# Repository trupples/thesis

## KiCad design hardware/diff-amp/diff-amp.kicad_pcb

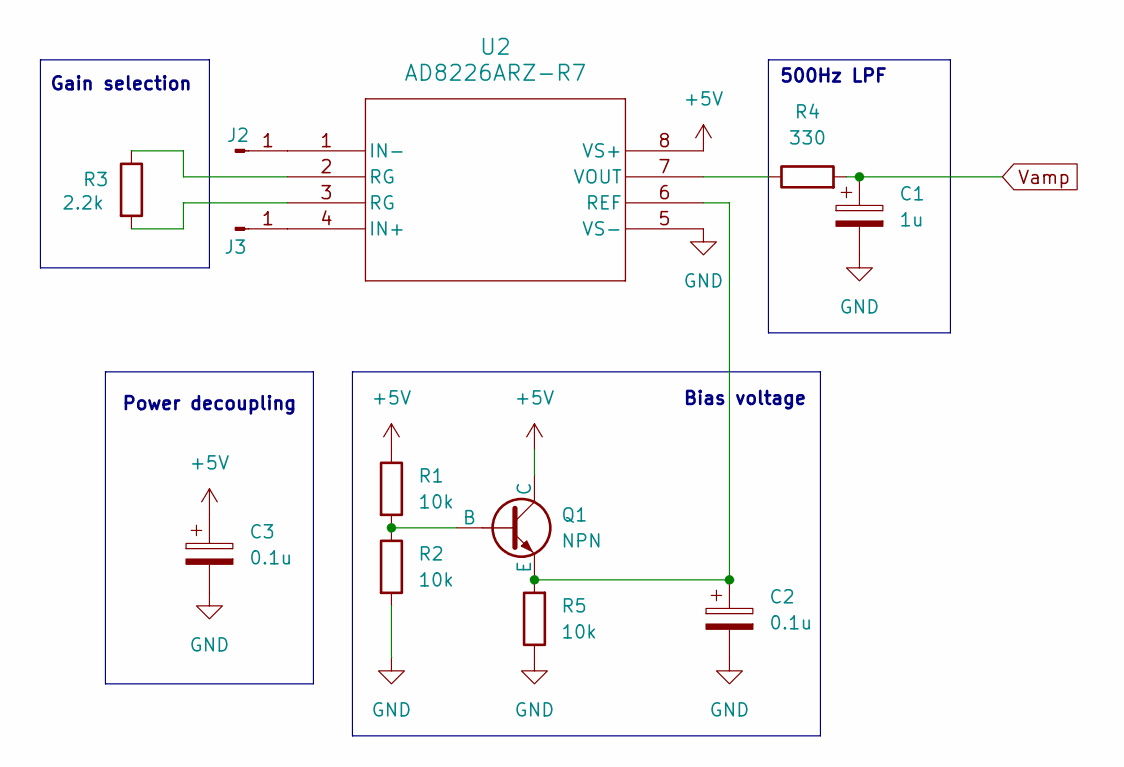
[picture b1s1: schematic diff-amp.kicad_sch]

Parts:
C1: 1u; CP_Radial_D4.0mm_P2.00mm
C2, C3: 0.1u; CP_Radial_D5.0mm_P2.50mm
J2, J3: Conn_01x01_Pin; SolderWirePad_1x01_SMD_5x10mm
Q1: NPN; TO-92L_Inline_Wide
R1, R2, R5: 10k; R_Axial_DIN0207_L6.3mm_D2.5mm_P2.54mm_Vertical
R3: 2.2k; R_Axial_DIN0207_L6.3mm_D2.5mm_P7.62mm_Horizontal
R4: 330; R_Axial_DIN0207_L6.3mm_D2.5mm_P10.16mm_Horizontal
U2: AD8226ARZ-R7; DIP-8_W7.62mm_Socket

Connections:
+5V: C3.1, Q1.1 (C), R1.1, U2.8 (VS+); also elsewhere on the board
GND: C1.2, C2.2, C3.2, R2.2, R5.1, U2.5 (VS-); also elsewhere on the board
unnamed: J2.1, U2.1 (IN-)
unnamed: J3.1, U2.4 (IN+)
unnamed: Q1.2 (B), R1.2, R2.1
unnamed: C2.1, Q1.3 (E), R5.2, U2.6 (REF)
unnamed: R3.1, U2.2 (RG)
unnamed: R3.2, U2.3 (RG)
unnamed: R4.1, U2.7 (VOUT)
Vout: C1.1, R4.2; also elsewhere on the board

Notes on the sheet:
500Hz LPF
Power decoupling
Gain selection
Bias voltage

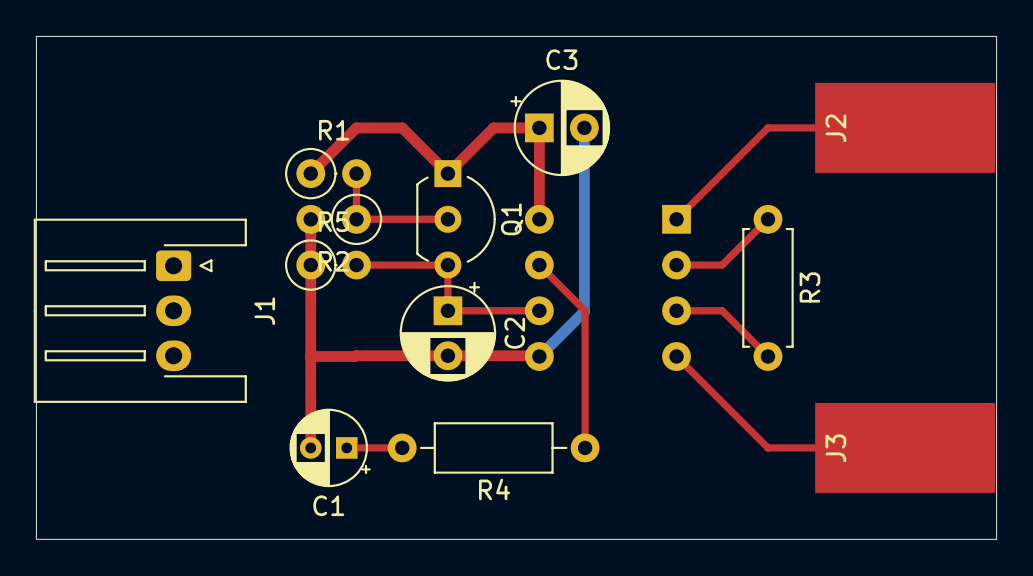
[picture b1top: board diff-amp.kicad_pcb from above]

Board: 2 copper layers, 53.3 x 27.9 mm, 13 parts (1 on the bottom side), 10 nets.

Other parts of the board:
J1: Conn_01x03_Socket; JST_XH_S3B-XH-A-1_1x03_P2.50mm_Horizontal

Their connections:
+5V: J1.1; also elsewhere on the board
GND: J1.2; also elsewhere on the board
Vout: J1.3; also elsewhere on the board

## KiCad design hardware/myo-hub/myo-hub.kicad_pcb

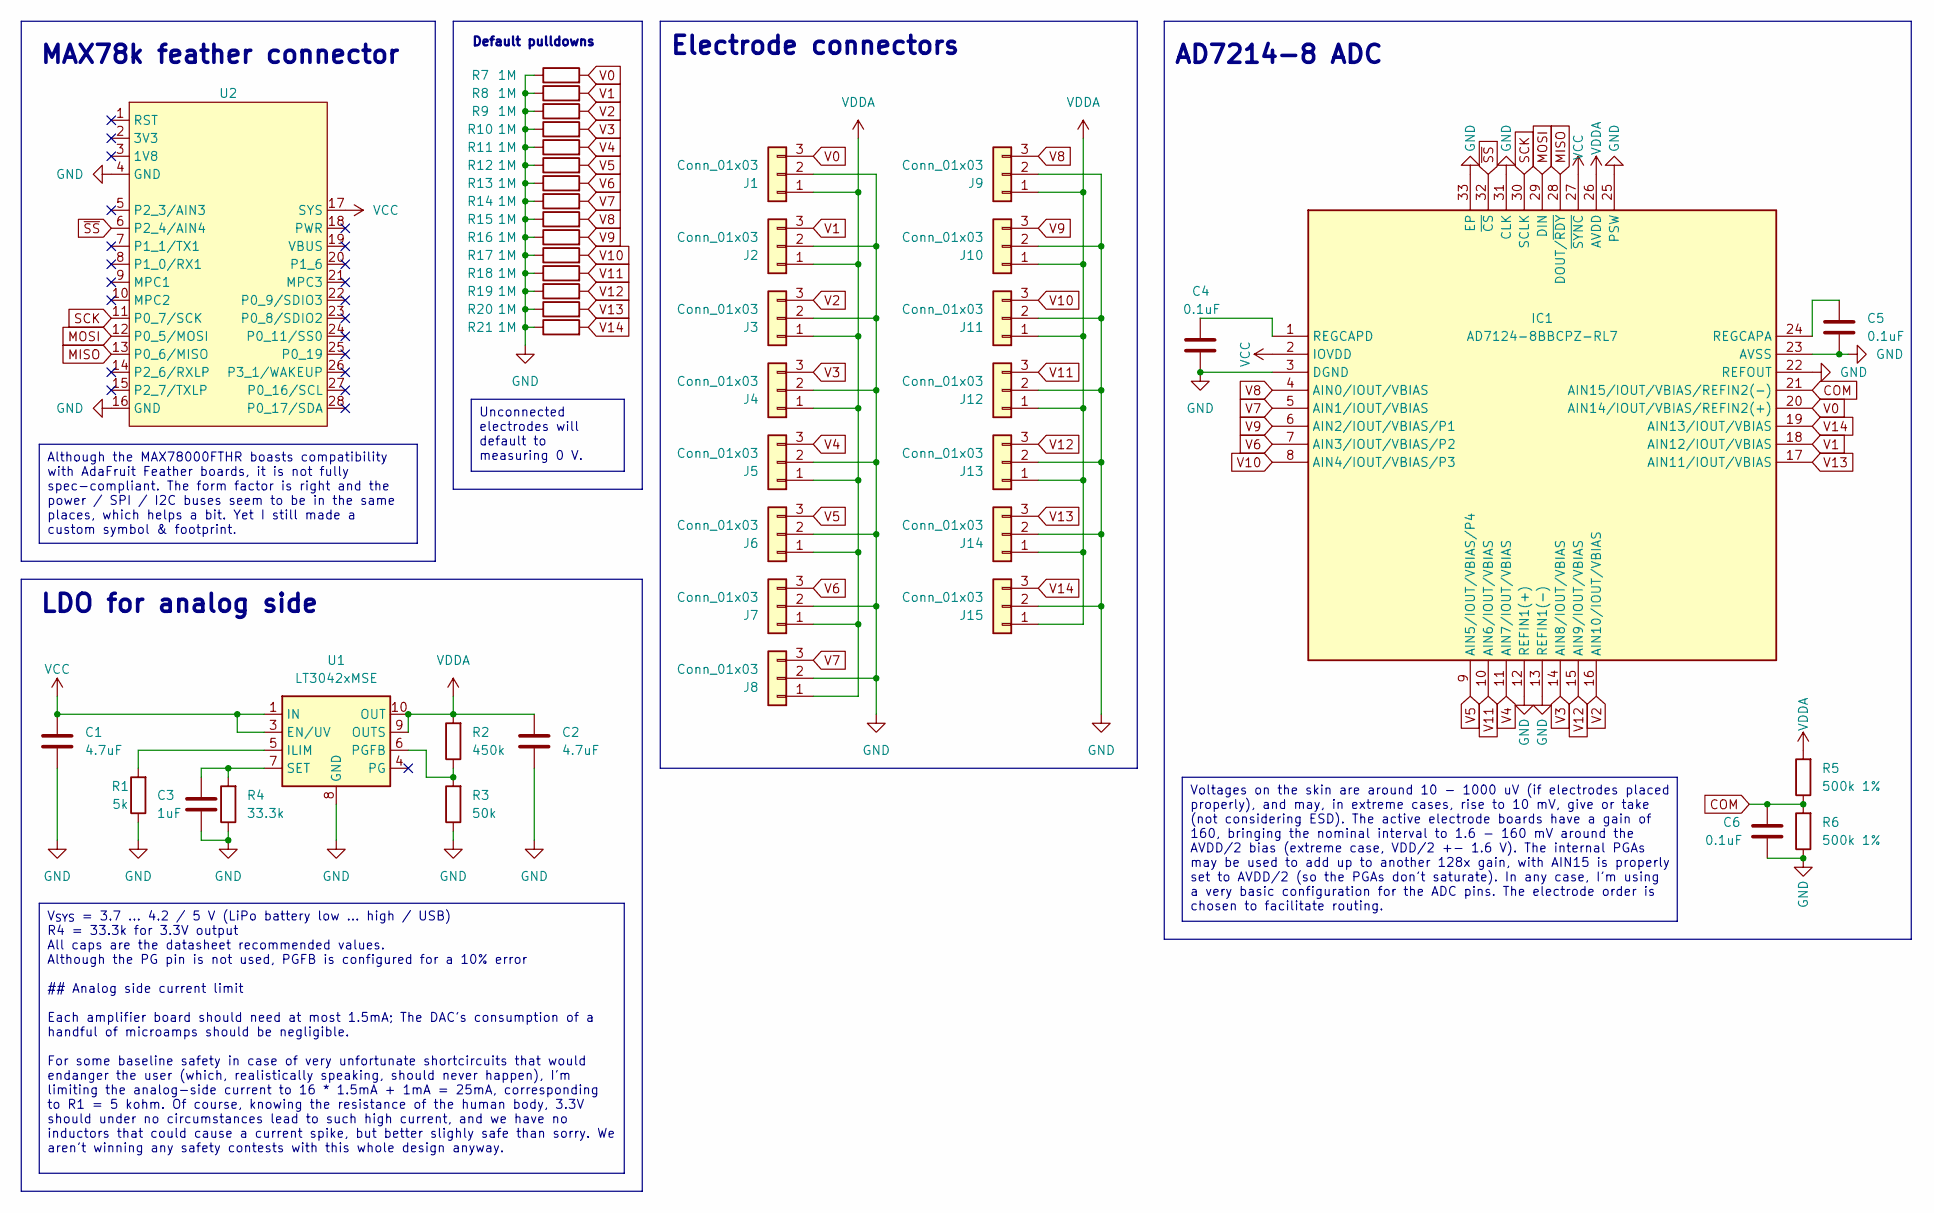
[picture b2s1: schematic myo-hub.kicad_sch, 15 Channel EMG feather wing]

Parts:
C1, C2: 4.7uF; C_0603_1608Metric_Pad1.08x0.95mm_HandSolder
C3: 1uF; C_0603_1608Metric_Pad1.08x0.95mm_HandSolder
C4, C5, C6: 0.1uF; C_0603_1608Metric_Pad1.08x0.95mm_HandSolder
IC1: AD7124-8BBCPZ-RL7; QFN50P500X500X100-33N-D; Mouser Part Number 584-AD7124-8BBCPZRL7
J1, J2, J3, J4, J5, J6, J7, J8, J9, J10, J11, J12, J13, J14, J15: Conn_01x03; JST_PH_B3B-PH-K_1x03_P2.00mm_Vertical
R1: 5k; R_0603_1608Metric_Pad0.98x0.95mm_HandSolder
R2: 450k; R_0603_1608Metric_Pad0.98x0.95mm_HandSolder
R3: 50k; R_0603_1608Metric_Pad0.98x0.95mm_HandSolder
R4: 33.3k; R_0603_1608Metric_Pad0.98x0.95mm_HandSolder
R5, R6: 500k 1%; R_0603_1608Metric_Pad0.98x0.95mm_HandSolder
R7, R8, R9, R10, R11, R12, R13, R14, R15, R16, R17, R18, R19, R20, R21: 1M; R_0603_1608Metric_Pad0.98x0.95mm_HandSolder
U1: LT3042xMSE; MSOP-10-1EP_3x3mm_P0.5mm_EP1.68x1.88mm
U2: MAX78000FTHR_Socket

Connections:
COM: C6.1, IC1.21 (AIN15/IOUT/VBIAS/REFIN2(-)), R5.1, R6.2
GND: C1.2, C2.2, C3.2, C4.1, C5.2, C6.2, IC1.3 (DGND), IC1.12 (REFIN1(+)), IC1.13 (REFIN1(-)), IC1.22 (REFOUT), IC1.23 (AVSS), IC1.25 (PSW), IC1.31 (CLK), IC1.33 (EP), J1.2, J2.2, J3.2, J4.2, J5.2, J6.2, J7.2, J8.2, J9.2, J10.2, J11.2, J12.2, J13.2, J14.2, J15.2, R1.1, R3.1, R4.1, R6.1, R7.1, R8.1, R9.1, R10.1, R11.1, R12.1, R13.1, R14.1, R15.1, R16.1, R17.1, R18.1, R19.1, R20.1, R21.1, U1.8 (GND), U1.11 (GND), U2.4 (GND), U2.16 (GND)
MISO: IC1.28 (DOUT/~RDY), U2.13 (P0_6/MISO)
MOSI: IC1.29 (DIN), U2.12 (P0_5/MOSI)
unnamed: C5.1, IC1.24 (REGCAPA)
unnamed: C4.2, IC1.1 (REGCAPD)
unnamed: R1.2, U1.5 (ILIM)
unnamed: R2.1, R3.2, U1.6 (PGFB)
unnamed: C3.1, R4.2, U1.7 (SET)
SCK: IC1.30 (SCLK), U2.11 (P0_7/SCK)
V0: IC1.20 (AIN14/IOUT/VBIAS/REFIN2(+)), J1.3, R7.2
V1: IC1.18 (AIN12/IOUT/VBIAS), J2.3, R8.2
V2: IC1.16 (AIN10/IOUT/VBIAS), J3.3, R9.2
V3: IC1.14 (AIN8/IOUT/VBIAS), J4.3, R10.2
V4: IC1.11 (AIN7/IOUT/VBIAS), J5.3, R11.2
V5: IC1.9 (AIN5/IOUT/VBIAS/P4), J6.3, R12.2
V6: IC1.7 (AIN3/IOUT/VBIAS/P2), J7.3, R13.2
V7: IC1.5 (AIN1/IOUT/VBIAS), J8.3, R14.2
V8: IC1.4 (AIN0/IOUT/VBIAS), J9.3, R15.2
V9: IC1.6 (AIN2/IOUT/VBIAS/P1), J10.3, R16.2
V10: IC1.8 (AIN4/IOUT/VBIAS/P3), J11.3, R17.2
V11: IC1.10 (AIN6/IOUT/VBIAS), J12.3, R18.2
V12: IC1.15 (AIN9/IOUT/VBIAS), J13.3, R19.2
V13: IC1.17 (AIN11/IOUT/VBIAS), J14.3, R20.2
V14: IC1.19 (AIN13/IOUT/VBIAS), J15.3, R21.2
VCC: C1.1, IC1.2 (IOVDD), IC1.27 (~SYNC), U1.1 (IN), U1.2 (IN), U1.3 (EN/UV), U2.17 (SYS)
VDDA: C2.1, IC1.26 (AVDD), J1.1, J2.1, J3.1, J4.1, J5.1, J6.1, J7.1, J8.1, J9.1, J10.1, J11.1, J12.1, J13.1, J14.1, J15.1, R2.2, R5.2, U1.9 (OUTS), U1.10 (OUT)
~SS: IC1.32 (~CS), U2.6 (P2_4/AIN4)

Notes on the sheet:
Voltages on the skin are around 10 - 1000 uV (if electrodes placed properly), and may, in extreme cases, rise to 10 mV, give or take (not considering ESD). The active electrode boards have a gain of 160, bringing the nominal interval to 1.6 - 160 mV around the AVDD/2 bias (extreme case, VDD/2 +- 1.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
Although the MAX78000FTHR boasts compatibility with AdaFruit Feather boards, it is not fully spec-compliant. The form factor is right and the power / SPI / I2C buses seem to be in the same places, which helps a bit. Yet I still made a custom symbol & footprint.
V_{SYS} = 3.7 ... 4.2 / 5 V (LiPo battery low ... high / USB) R4 = 33.3k for 3.3V output All caps are the datasheet recommended values. Although the PG pin is not used, PGFB is configured for a 10% error ## Analog side current limit Each amplifier board should need at most 1.5mA; The DAC's consumpt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
Unconnected electrodes will default to measuring 0 V.
Electrode connectors
Default pulldowns
LDO for analog side
MAX78k feather connector
AD7214-8 ADC

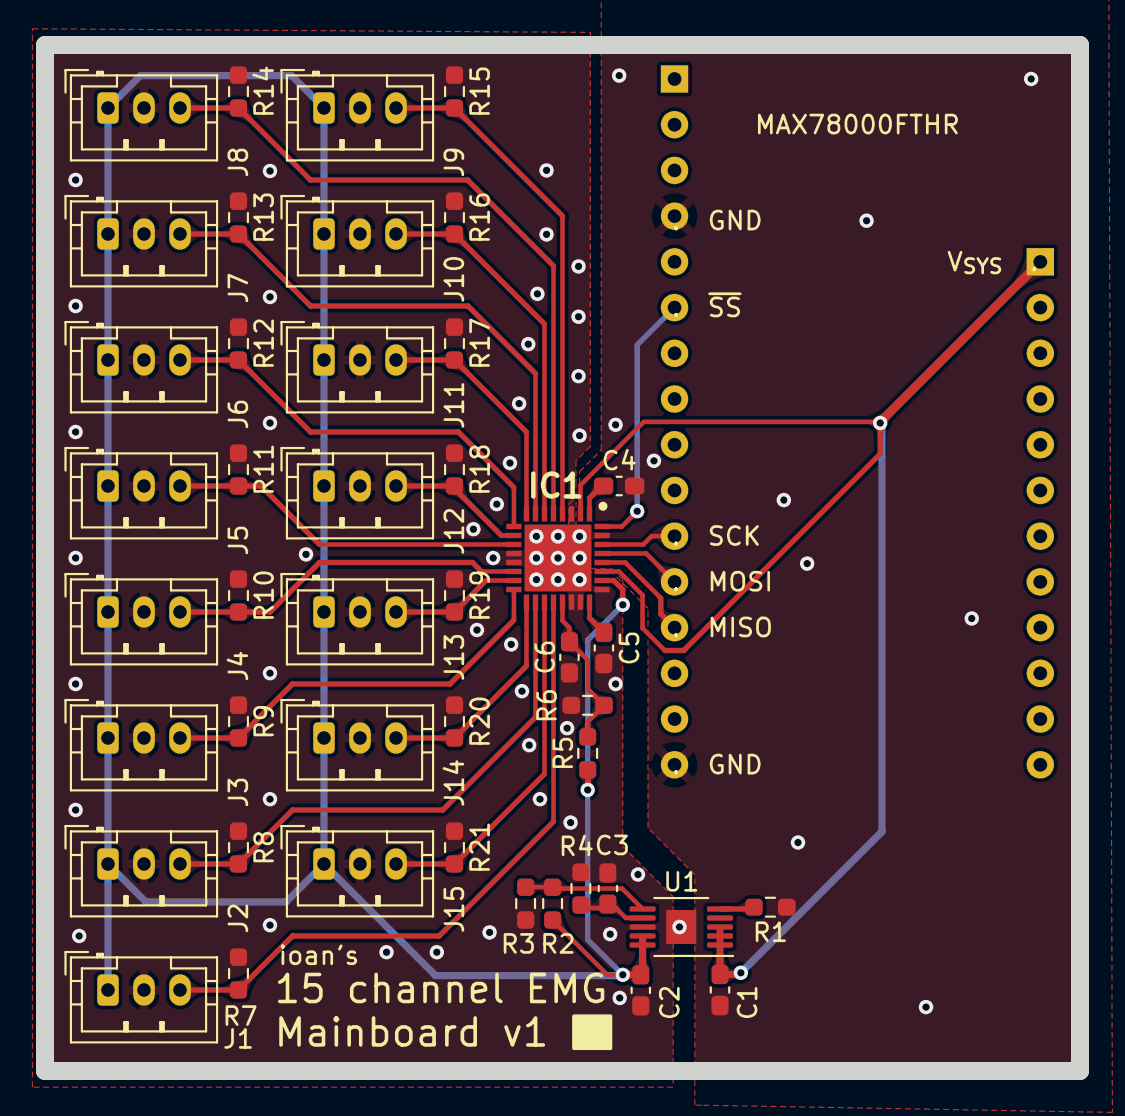
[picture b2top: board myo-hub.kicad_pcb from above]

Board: 2 copper layers, 57.5 x 57.0 mm, 45 parts (0 on the bottom side), 28 nets.

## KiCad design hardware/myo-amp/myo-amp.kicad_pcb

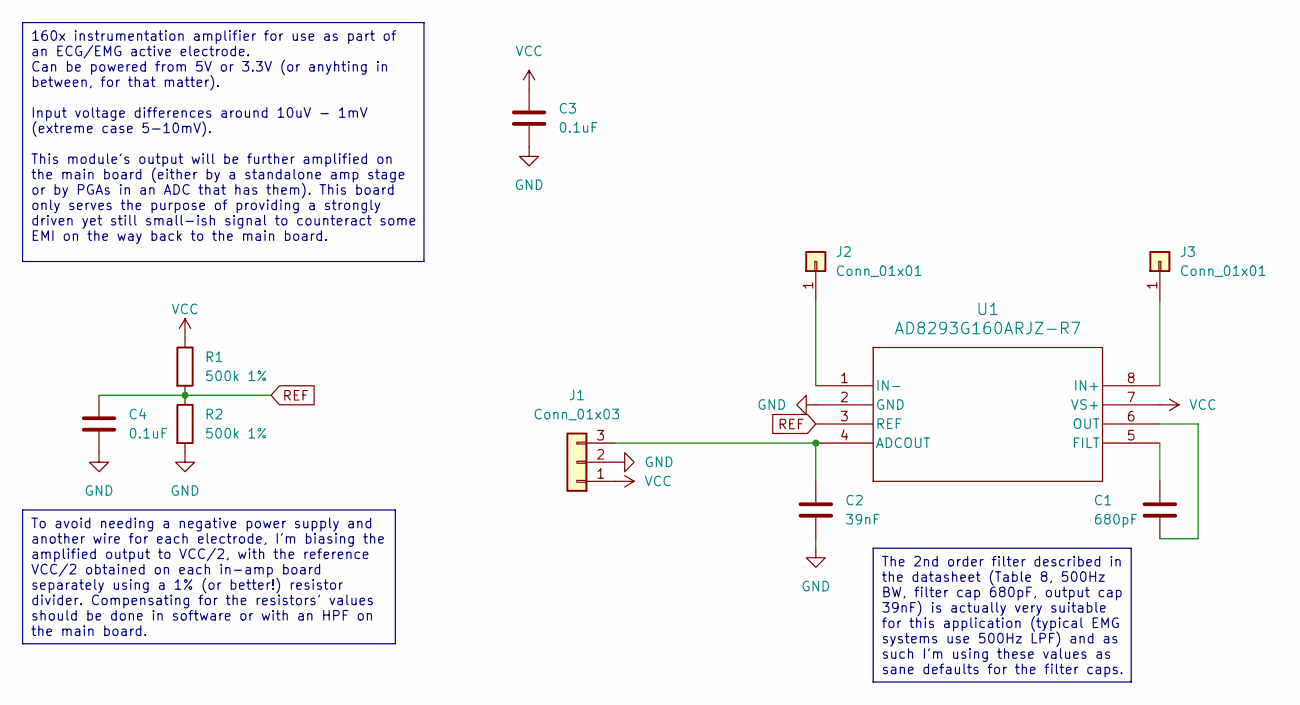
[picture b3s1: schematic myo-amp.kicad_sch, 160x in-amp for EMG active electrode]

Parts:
C1: 680pF; C_0603_1608Metric_Pad1.08x0.95mm_HandSolder
C2: 39nF; C_0603_1608Metric_Pad1.08x0.95mm_HandSolder
C3, C4: 0.1uF; C_0603_1608Metric_Pad1.08x0.95mm_HandSolder
J1: Conn_01x03; JST_PH_S3B-PH-K_1x03_P2.00mm_Horizontal
J2, J3: Conn_01x01; SolderWire-0.5sqmm_1x01_D0.9mm_OD2.1mm_Relief
R1, R2: 500k 1%; R_0603_1608Metric_Pad0.98x0.95mm_HandSolder
U1: AD8293G160ARJZ-R7; SOT-23-8_Handsoldering

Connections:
+5V: C3.1, J1.1, R1.1, U1.7 (VS+)
GND: C2.2, C3.2, C4.2, J1.2, R2.2, U1.2 (GND)
unnamed: C2.1, J1.3, U1.4 (ADCOUT)
unnamed: J2.1, U1.1 (IN-)
unnamed: J3.1, U1.8 (IN+)
unnamed: C1.2, U1.5 (FILT)
unnamed: C1.1, U1.6 (OUT)
REF: C4.1, R1.2, R2.1, U1.3 (REF)

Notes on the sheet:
The 2nd order filter described in the datasheet (Table 8, 500Hz BW, filter cap 680pF, output cap 39nF) is actually very suitable for this application (typical EMG systems use 500Hz LPF) and as such I'm using these values as sane defaults for the filter caps.
To avoid needing a negative power supply and another wire for each electrode, I'm biasing the amplified output to VCC/2, with the reference VCC/2 obtained on each in-amp board separately using a 1% (or better!) resistor divider. Compensating for the resistors' values should be done in software or w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
160x instrumentation amplifier for use as part of an ECG/EMG active electrode. Can be powered from 5V or 3.3V (or anyhting in between, for that matter). Input voltage differences around 10uV - 1mV (extreme case 5-10mV). This module's output will be further amplified on the main board (either by a s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

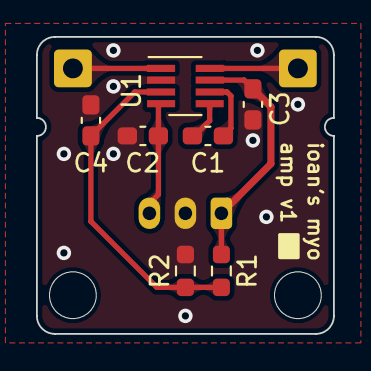
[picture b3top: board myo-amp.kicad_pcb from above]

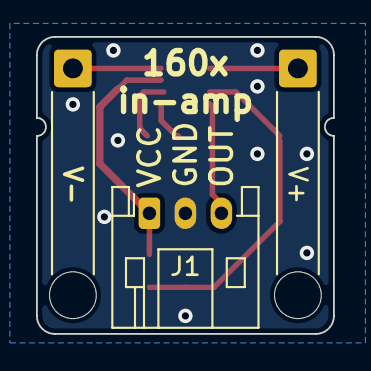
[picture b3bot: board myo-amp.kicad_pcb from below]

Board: 2 copper layers, 16.5 x 16.5 mm, 10 parts (3 on the bottom side), 8 nets.

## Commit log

2024-03-09 Update documentation
2024-03-10 2024-03-10
2024-04-24 Amplifier board hardware for review
2024-04-24 WIP main feather wings
    One of the main issues to address would be that I wrongly (and greedily) picked the AD4310 which is rather limited samplerate-wise. Considering changing to the AD7124-8 for 15 channels
2024-04-24 Remove files that should have been gitignored
2024-04-24 Change ADC to AD7124-8
2024-04-24 Mainboard silkscreen, ground vias, routing tweaks
2024-04-24 Tidy mainboard schematic
2024-04-24 Mainboard layout cleanup
2024-04-29 Add pseudo-differential reference circuit
    This in turn enables us to use the PGAs without saturating them.
    With a zero reference, we can only use gain=1, because even gain=2
    would result in a AVDD/2*2 = AVDD voltage at the PGA's output with
    zero! input.
2024-04-29 Move all components to primary side
2024-05-21 WIP firmware
2024-05-21 first time getting some data back
2024-05-24 Tweak VS code config and makefile
2024-05-24 Create custom EXG IIO device description
2024-05-24 Add Barbero2012 to gitignore
2024-05-24 Remove README copied from SPI demo
2024-05-24 Add old notes from 2 months ago
2024-05-28 One channel measurements 128x work :D
2024-06-02 Add flash erase task
    Helpful when the debugger cant connect anymore
2024-06-02 Logs 2024-06-03 v incomplete
2024-06-10 2024-06 single channel ECG measurements
2024-06-10 2024-06-10 2k words on the train
2024-06-11 AD4114 single channel measurements
2024-06-11 firmware-side IIO progress
2024-06-13 Multi channel working woah
2024-06-17 GPIO IRQ attempt to get /RDY. Fail :(
2024-06-18 Half working timer interrupt trigger
2024-06-18 Change to usual no-os project structure
2024-06-20 Bodges to try to get the hardware timer to work
    IIO resets the IRQ controller when starting up (iio_app_init > print_uart_hello_message > no_os_uart_remove > max_uart_remove > no_os_irq_ctrl_remove) which is a bummer. Reference count logic is brok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
2024-06-24 Initial latex, 14 hungry pages out of 40
2024-06-25 Nothing works :^)
2024-06-27 IT SORT OF WORKS
2024-07-05 i am very behind schedule
2024-08-21 physiology finally + a little signal chain stuff
2024-08-31 Preamp board DONE and written up GOD
2024-09-01 last night text
2024-09-01 99% final firmware
    Only improvement point would be some filtering but it seems like thats not needed
2024-09-01 iio demos DONE
2024-09-01 Software DONE
2024-09-02 caffeine checkpoint
2024-09-02 checkpoint
2024-09-02 FIRST SUFFICIENT DRAFT
2024-09-02 firmware software checkpoint
2024-09-02 new cover
2025-06-29 File cleanup
2025-06-30 Minor changes
    * Change ROS2 to ROS 2
    * Change LibIIO to libiio
    * Rephrase some paragraphs (more to come ASAP)
2025-07-07 text tweaks
2025-07-07 cover 2025
